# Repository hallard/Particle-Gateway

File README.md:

Particle (formerly Spark) Gateway
=================================

Edit October 2015 : New Revision 1.0a with better SMA connector for RF module

The gateway can host several funny things like

- Socket to plug a Spark Core or Particle Photon
- Pins to connect I2C or SPI OLED 128x64
- Pins to connect 2.2" or 1.8" TFT LCD
- RFM69 or RFM12B on board module
- Lipo Battery connector for testing and move the Gateway (no charger on board)
- 3V3 On board regulator for harvesting devices if any to avoid pumping from Particle Regulator
- Data connection for any cheap ebay ASK RX receiver
- FTDI connection for those who want to debug serial or send data over real serial
- 2 x grove I2C connector to connect other I2C devices

Detailed Description
====================

Everything is documented on this dedicated [post][1] 

### Schematic  

### Bill Of Material
Reference from Seeedstudio [Open Part Libray][8] SKU but can be ordered on any provider, Digikey, Mouser. Link to the [BOM][6] file.    

For SPARK connector I use IC socket that I cut on needed size, for other connectors, I usually buy 40 pins headers (male and female) on ebay that I cut at the needed size. [Example][7]

### Boards  
&nbsp;
&nbsp; 

You can order the PCB of this board at [OSHPARK][5]

### Assembled boards

&nbsp;

&nbsp; 

##License

You can do whatever you like with this design.

##Misc
See news and other projects on my [blog][2] 
 
[1]: https://hallard.me/particle-gateway/
[2]: https://hallard.me
[3]: https://github.com/thibdct/programmateur-fil-pilote-wifi/tree/master/Logiciel/remora
[4]: http://lowpowerlab.com/blog/2013/06/20/rfm69-library/
[5]: https://oshpark.com/shared_projects/S3Dmdwhs
[6]: https://github.com/hallard/Particle-Gateway/blob/master/Particle-Gateway-BOM.xlsx?raw=true
[7]: http://stores.ebay.com/jkpartsstore/Connectors-Sockets-/_i.html?_fsub=1665035011
[8]: http://www.seeedstudio.com/depot/OPLopen-parts-library-catalog-c-136_138/?ref=side

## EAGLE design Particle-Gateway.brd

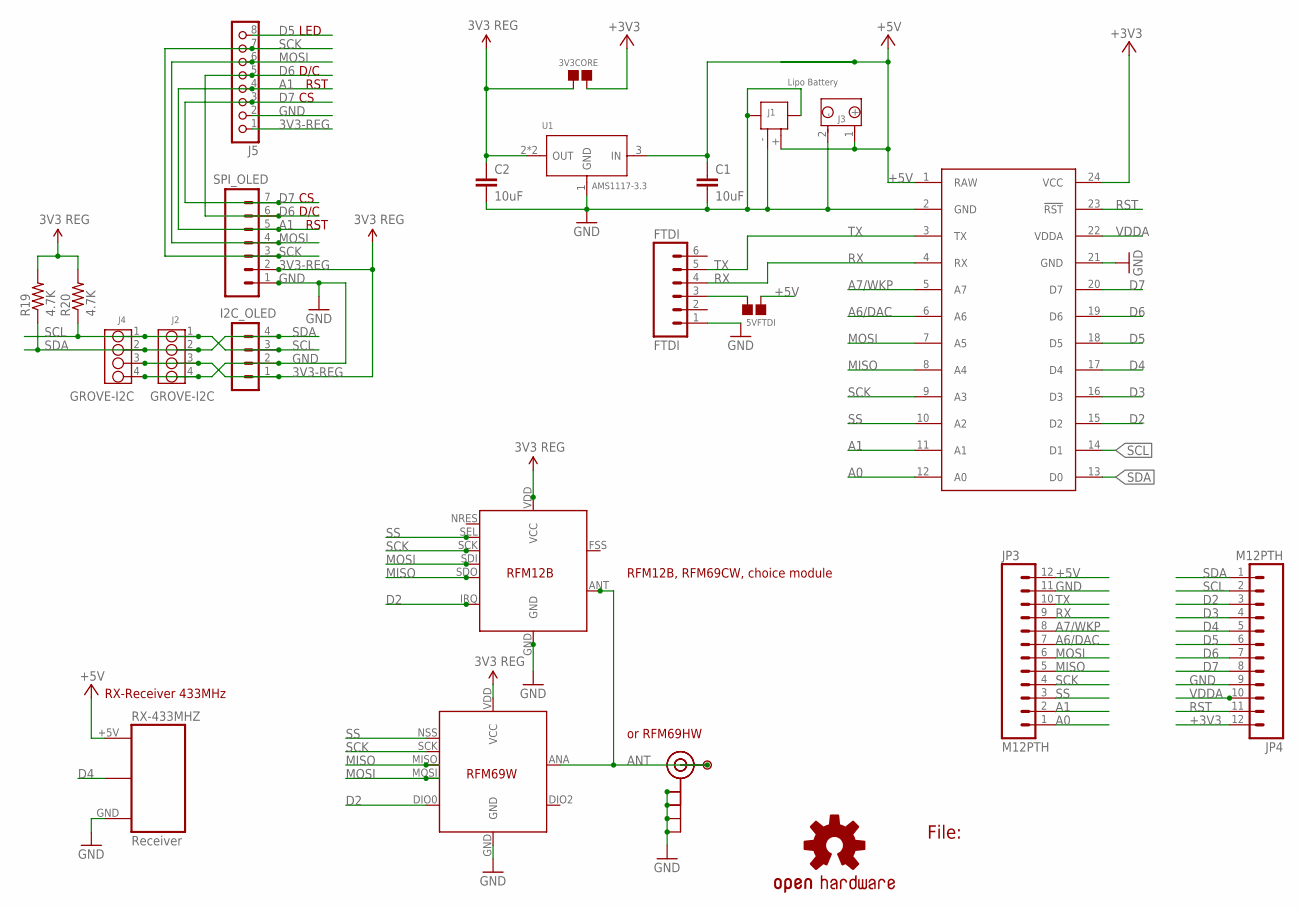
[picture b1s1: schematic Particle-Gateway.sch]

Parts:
3V3CORE, 5VFTDI: PAD-JUMPER-2P; 2P-SMD-1.78X1.27
C1, C2: 10uF; 0805-CAP
FTDI: FTDI; 1X06
I2C_OLED: CON_HEADER_1X04'SMALL''; M1X4
J1: JST-2P-SMD'2.0'; 2P-SMD-2.0-90D
J2: GROVE-I2C; 4P-2.0-90D
J3: Lipo Battery; 2P-2.0-90D
J4: GROVE-I2C; 4P-2.0
J5: CON_HEADER_1X08-PTH; M1X8
J$1: SMA_EDGE; SMA-EDGE
JP3, JP4: M12PTH; 1X12-SMALL-PADS
LOGO2: OSHW-LOGOL; OSHW-LOGO-L
P1: PADSMALL; PAD-SMALL
R19, R20: 4.7K; 0805-RES
RX-433MHZ: Receiver; RF-LINK_RX_NO_SILK
SPARKCORE: SPARK_CORECORE; SPARK_CORE
SPI_OLED: CON_HEADER_1X07'SMALL'; M1X7
U1: AMS1117-3.3; SOT223
U$2: RFM12B; RFM12B-MINPADS
U$3: RFM69W; RFM69W-MINPADS
U-FL: U.FL

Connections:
3V3-REG: 3V3CORE.1, C2.1, I2C_OLED.1, J2.3, J4.3, J5.1, R19.2, R20.2, SPI_OLED.2, U1.2 (OUT), U1.TER (OUT), U$2.VDD (VCC), U$3.VDD (VCC)
+3V3: 3V3CORE.2, JP4.12, SPARKCORE.24 (VCC)
+5V: 5VFTDI.1, C1.1, J1.+ (1), J3.1 (+), JP3.12, RX-433MHZ.+5V, SPARKCORE.1 (RAW), U1.3 (IN)
A0: JP3.1, SPARKCORE.12 (A0)
A1: J5.4, JP3.2, SPARKCORE.11 (A1), SPI_OLED.5
A6/DAC: JP3.7, SPARKCORE.6 (A6)
A7/WKP: JP3.8, SPARKCORE.5 (A7)
ANT: J$1.SIG (SIGNAL), P1.1, U$2.ANT, U$3.ANA (ANT), U-FL.3 (SIGNAL)
D2: JP4.3, SPARKCORE.15 (D2), U$2.IRQ, U$3.DIO0
D3: JP4.4, SPARKCORE.16 (D3)
D4: JP4.5, RX-433MHZ.DATA@1 (DATA), RX-433MHZ.DATA@2 (DATA), SPARKCORE.17 (D4)
D5: J5.8, JP4.6, SPARKCORE.18 (D5)
D6: J5.5, JP4.7, SPARKCORE.19 (D6), SPI_OLED.6
D7: J5.3, JP4.8, SPARKCORE.20 (D7), SPI_OLED.7
GND: C1.2, C2.2, FTDI.1, I2C_OLED.2, J1.3, J1.4, J1.- (2), J2.4, J3.2 (-), J4.4, J5.2, J$1.GND@0 (GND), J$1.GND@1 (GND), J$1.GND@2 (GND), J$1.GND@3 (GND), JP3.11, JP4.9, RX-433MHZ.GND, SPARKCORE.2 (GND), SPARKCORE.21 (GND), SPI_OLED.1, U1.1 (GND), U$2.GND, U$3.GND, U-FL.1 (GND), U-FL.2 (GND)
MISO: JP3.5, SPARKCORE.8 (A4), U$2.SDO, U$3.MISO
MOSI: J5.6, JP3.6, SPARKCORE.7 (A5), SPI_OLED.4, U$2.SDI, U$3.MOSI
unnamed: 5VFTDI.2, FTDI.3
RST: JP4.11, SPARKCORE.23 (!RST)
RX: FTDI.4, JP3.9, SPARKCORE.4 (RX)
SCK: J5.7, JP3.4, SPARKCORE.9 (A3), SPI_OLED.3, U$2.SCK, U$3.SCK
SCL: I2C_OLED.3, J2.1, J4.1, JP4.2, R20.1, SPARKCORE.14 (D1)
SDA: I2C_OLED.4, J2.2, J4.2, JP4.1, R19.1, SPARKCORE.13 (D0)
SS: JP3.3, SPARKCORE.10 (A2), U$2.SEL, U$3.NSS (SEL)
TX: FTDI.5, JP3.10, SPARKCORE.3 (TX)
VDDA: JP4.10, SPARKCORE.22 (VDDA)

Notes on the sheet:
RFM12B, RFM69CW, choice module
or RFM69HW
RX-Receiver 433MHz
D/C
LED
RST
File:

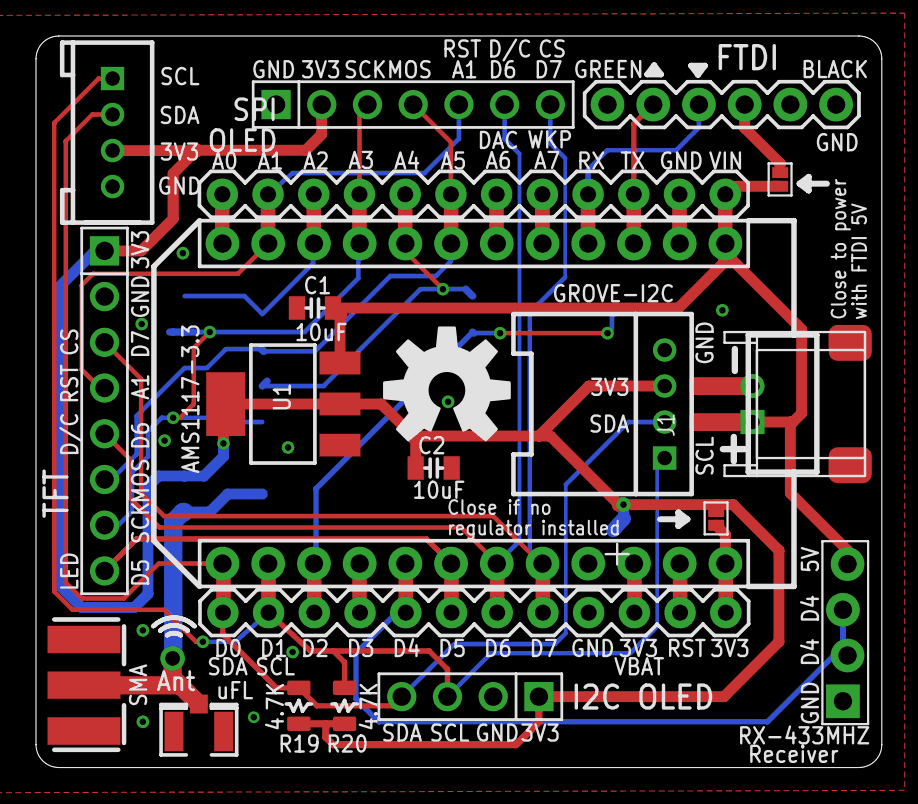
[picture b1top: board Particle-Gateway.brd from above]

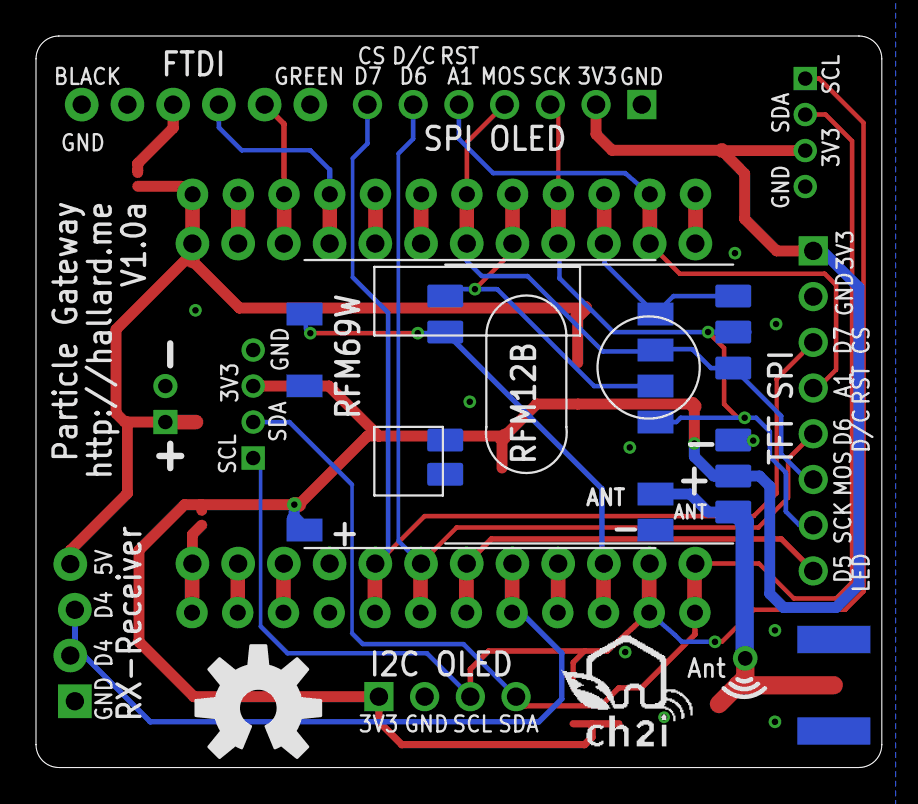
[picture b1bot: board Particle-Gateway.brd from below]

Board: 2 copper layers, 47.0 x 40.6 mm, 27 parts (4 on the bottom side), 26 nets.

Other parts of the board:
LOGO1: OSHW-LOGOL; OSHW-LOGO-L
U$1: LOGO_CH2I_75MM

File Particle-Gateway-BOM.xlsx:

Part | Value | Device | Package | Description | SEEEDSTUDIO OPL SKU
C1 | 10uF | CAP0805-CAP | 0805-CAP | Capacitor | 302010178
C2 | 10uF | CAP0805-CAP | 0805-CAP | Capacitor | 302010178
FTDI | FTDI | M06SIP | 1X06 | 6x2.54mm male header | 320020078
I2C_OLED | CON_HEADER_1X04'SMALL'' | CON_HEADER_1X04'SMALL'' | M1X4 | 4x2.54mm Female connector | 320030017
J1 |  | JST-2P-SMD'2.0' | 2P-SMD-2.0-90D | Battery Connector (Use J1 or J3 not both) | 320110027
J2 | GROVE-I2C | GROVE-4P-2.0-3470140P1 | 4P-2.0-90D | Grove connector | 320110034
J3 | Lipo Battery | JST-2P-PW-3410070P1 | 2P-2.0-90D | Battery Connector (Use J1 or J3 not both) | 320110026
J4 | GROVE-I2C | GROVE-4P-2.0-3470130P1 | 4P-2.0 | Grove connector | 320110033
J5 | CON_HEADER_1X08-PTH | CON_HEADER_1X08-PTH | M1X8 | 8x2.54mm Female connector | 320030061
JP3 | M12PTH | M12PTH | 1X12-SMALL-PADS | Header 12
JP4 | M12PTH | M12PTH | 1X12-SMALL-PADS | Header 12
R19 | 4.7K | RESISTOR0805-RES | 0805-RES | Resistor | 301010306
R20 | 4.7K | RESISTOR0805-RES | 0805-RES | Resistor | 301010306
SPI_OLED | CON_HEADER_1X07'SMALL' | CON_HEADER_1X07'SMALL' | M1X7 | 7x2.54mm Female connector | 320020093
U1 | AMS1117-3.3 | CJ1117-3.3-1310190P1 | SOT223 | 3V3 1A Low Dropout Linear Regulator | 310030097

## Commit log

2015-07-17 :confetti_ball: Added .gitattributes & .gitignore files
2015-07-17 Creation
2015-07-17 Added links
2015-07-17 Picture resizing
2015-08-27 Added eagle backup files
2015-09-08 Added BOM links
2015-09-08 Link correction
2015-09-08 Removed BOM link problem
2015-09-08 Fix presentation
2015-09-08 Presentation
2015-09-08 Type
2015-09-08 Links errors
2015-09-08 Added 1 picture with OLED
2015-09-08 Bad image position
2015-10-14 Adjusted SMA connector exposed PAD
2015-10-14 Revision 1.0a
2015-10-14 Updated new OSHPark link

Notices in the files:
parts and their libraries:
microbuilder: This work is placed in the public domain, and may be freely used for commercial and non-commercial work with the following conditions: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
SparkFun-Aesthetics: Licensing: Creative Commons ShareAlike 4.0 International - https://creativecommons.org/licenses/by-sa/4.0
